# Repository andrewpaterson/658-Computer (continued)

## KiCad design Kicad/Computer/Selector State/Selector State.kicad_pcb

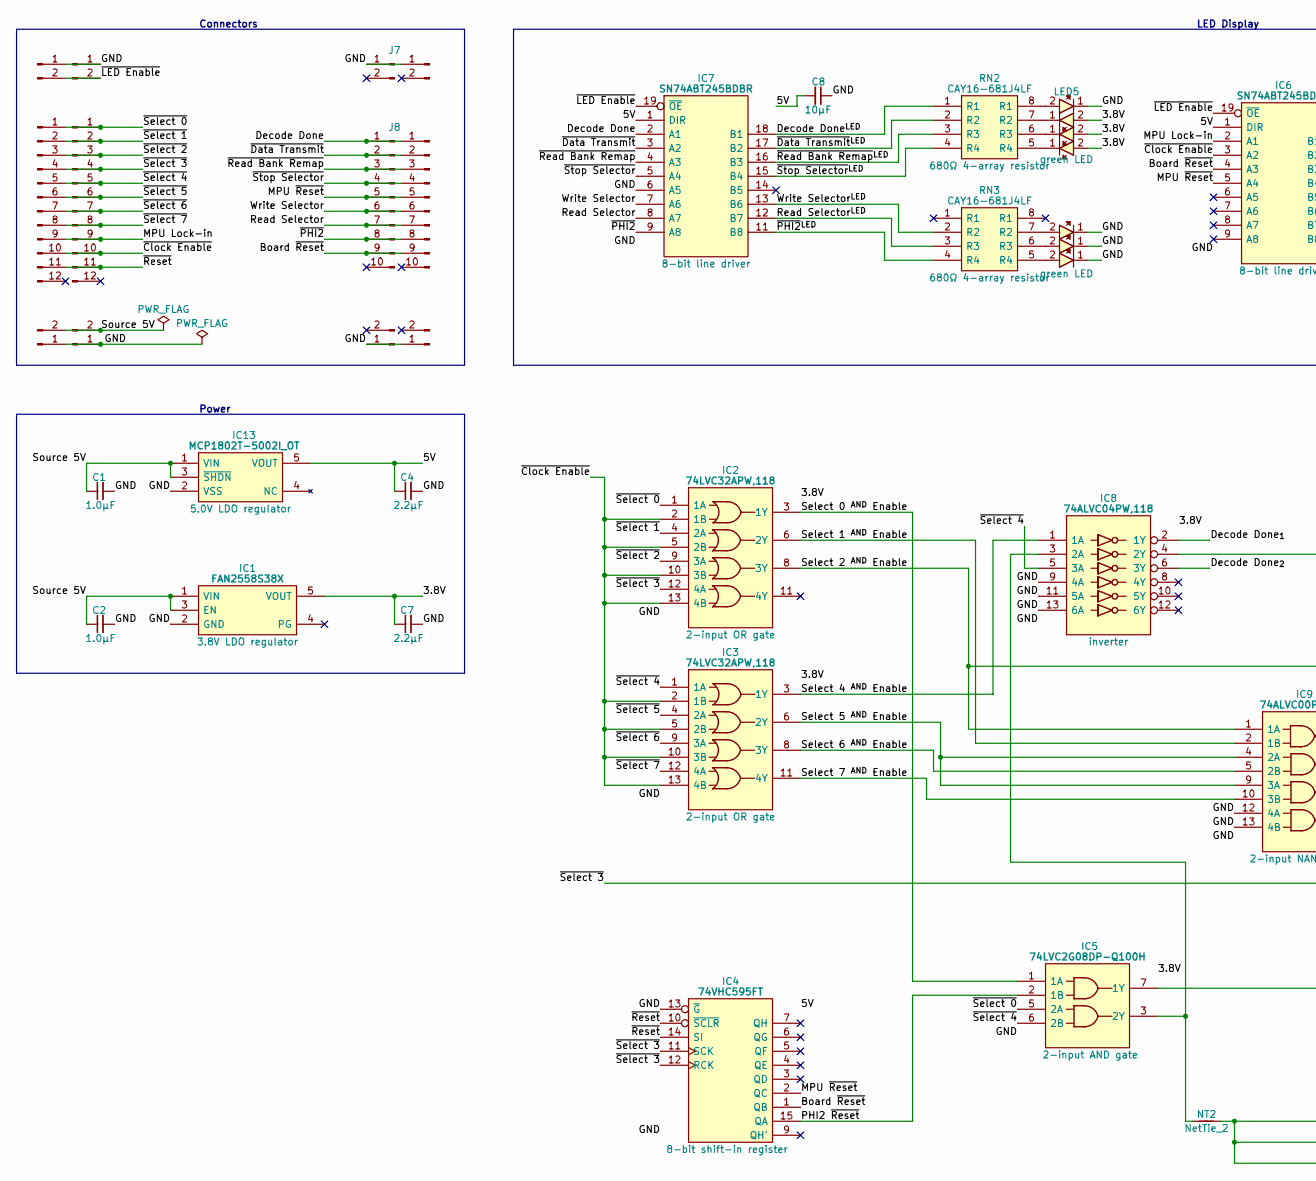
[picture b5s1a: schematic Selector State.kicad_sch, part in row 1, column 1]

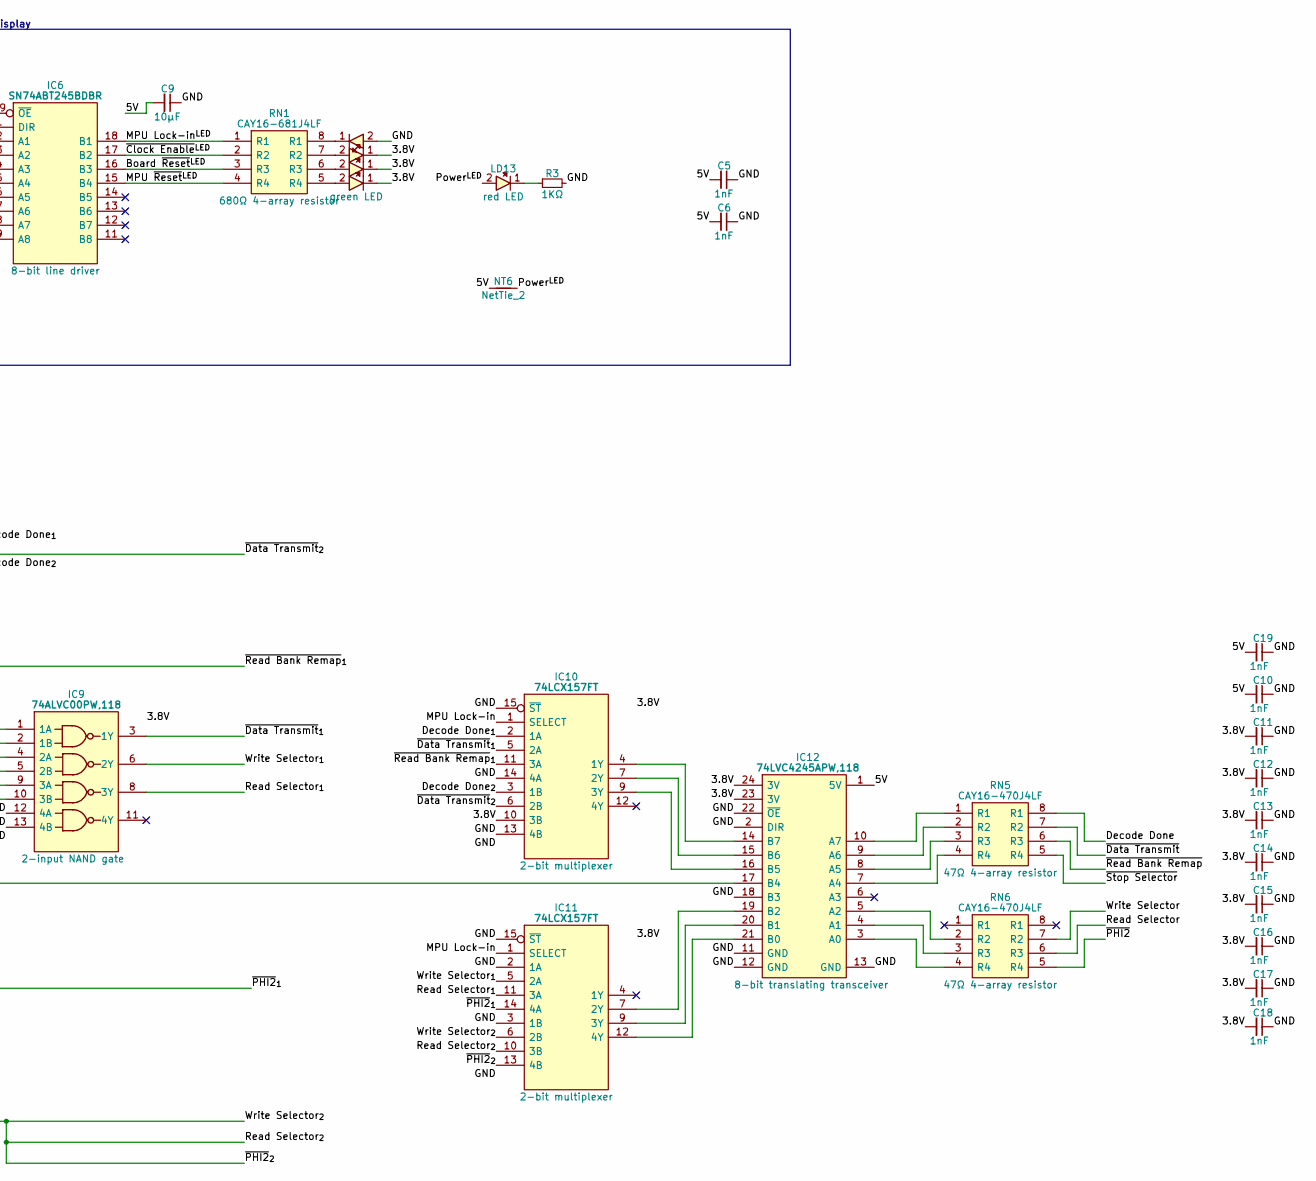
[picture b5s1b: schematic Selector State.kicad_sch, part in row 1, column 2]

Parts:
C1, C2, C4, C7: C_0805
C5, C6, C8, C9, C10, C11, C12, C13, C14, C15, C16, C17, C18, C19: C_Small; C_0805_2012Metric
IC1: FAN2558S38X; SOT95P270X145-5N; Manufacturer_Part_Number FAN2558S38X; Mouser Part Number 512-FAN2558S38X
IC2, IC3: 74LVC32APW,118; SOP65P640X110-14N; Manufacturer_Part_Number 74LVC32APW,118; Mouser Part Number 771-74LVC32APW-T
IC4: 74VHC595FT; SOP65P640X120-16N; Manufacturer_Part_Number 74VHC595FT; Mouser Part Number 757-74VHC595FT
IC5: 74LVC2G08DP-Q100H; SOP65P400X110-8N; Manufacturer_Part_Number 74LVC2G08DP-Q100H; Mouser Part Number 771-74LVC2G08DPQ100H
IC6, IC7: SN74ABT245BDBR; SOP65P780X200-20N; Manufacturer_Part_Number SN74ABT245BDBR; Mouser Part Number 595-SN74ABT245BDBR
IC8: 74ALVC04PW,118; SOP65P640X110-14N; Manufacturer_Part_Number 74ALVC04PW,118; Mouser Part Number 771-ALVC04PW118
IC9: 74ALVC00PW,118; SOP65P640X110-14N; Mouser Part Number 771-ALVC00PW118
IC10, IC11: 74LCX157FT; SOP65P640X120-16N; Manufacturer_Part_Number 74LCX157FT; Mouser Part Number 757-74LCX157FT
IC12: 74LVC4245APW,118; SOP65P640X110-24N; Mouser Part Number 771-74LVC4245APW-T
IC13: MCP1802T-5002I_OT; SOT95P270X145-5N; Manufacturer_Part_Number MCP1802T-5002I/OT; Mouser Part Number 579-MCP1802T-5002IOT
J1, J3, J4, J6, J7, J9, J10, J12: Conn_01x02_Male; PinHeader_1x02_P2.54mm_Vertical
J2, J5: Conn_01x12_Male; PinHeader_1x12_P2.54mm_Vertical
J8, J11: Conn_01x10_Male; PinHeader_1x10_P2.54mm_Vertical
LD10, LD11, LD12: 150224VS73100A; Manufacturer_Part_Number 150224VS73100A; Mouser Part Number 710-150224VS73100A
LD13: 150224SS73100; 150224SS73100A; Manufacturer_Part_Number 150224SS73100; Mouser Part Number 710-150224SS73100
LED1, LED2, LED3, LED4, LED5, LED6, LED7, LED8: 150224VS73100A; Manufacturer_Part_Number 150224VS73100A; Mouser Part Number 710-150224VS73100A
NT2, NT6: NetTie_2; NetTie-2_SMD_Pad0.5mm
R3: R_0805
RN1, RN2, RN3: CAY16-681J4LF; CAY16-J4; Manufacturer_Part_Number CAY16-681J4LF; Mouser Part Number 652-CAY16-681J4LF
RN5, RN6: CAY16-470J4LF; CAY16470J4LF; Manufacturer_Part_Number CAY16-470J4LF; Mouser Part Number 652-CAY16-470J4LF

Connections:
/3.8V: C7.1, C11.2, C12.2, C13.2, C14.2, C15.2, C16.2, C17.2, C18.2, IC1.5 (VOUT), IC2.14 (3V), IC3.14 (3V), IC5.8 (3V), IC8.14 (3V), IC9.14 (3V), IC10.10 (3B), IC10.16 (3V), IC11.16 (3V), IC12.23 (3V), IC12.24 (3V), LED2.1, LED3.1, LED4.1, LED6.2, LED7.2, LED8.2
/5V: C4.1, C5.2, C6.2, C8.2, C9.2, C10.2, C19.2, IC4.16 (5V), IC6.1 (DIR), IC6.20 (5V), IC7.1 (DIR), IC7.20 (5V), IC12.1 (5V), IC13.5 (VOUT), NT6.1
/Board ~Reset: IC4.1 (QB), IC6.4 (A3), J8.9, J11.9
/Board ~Reset^{LED}: IC6.16 (B3), RN1.3 (R3)
/Decode Done: IC7.2 (A1), J8.1, J11.1, RN5.8 (R1)
/Decode Done^{LED}: IC7.18 (B1), RN2.1 (R1)
/Decode Done_{1}: IC8.2 (1Y), IC10.2 (1A)
/Decode Done_{2}: IC8.6 (3Y), IC10.3 (1B)
/GND: C1.2, C2.2, C4.2, C5.1, C6.1, C7.2, C8.1, C9.1, C10.1, C11.1, C12.1, C13.1, C14.1, C15.1, C16.1, C17.1, C18.1, C19.1, IC1.2 (GND), IC2.7 (GND), IC3.7 (GND), IC4.8 (GND), IC4.13 (~G), IC5.4 (GND), IC6.10 (GND), IC7.6 (A5), IC7.10 (GND), IC8.7 (GND), IC8.9 (4A), IC8.11 (5A), IC8.13 (6A), IC9.7 (GND), IC9.12 (4A), IC9.13 (4B), IC10.8 (GND), IC10.13 (4B), IC10.14 (4A), IC10.15 (~ST), IC11.2 (1A), IC11.3 (1B), IC11.8 (GND), IC11.15 (~ST), IC12.2 (DIR), IC12.11 (GND), IC12.12 (GND), IC12.13 (GND), IC12.18 (B3), IC12.22 (~OE), IC13.2 (VSS), J1.1, J3.1, J4.1, J6.1, J7.1, J9.1, J10.1, J12.1, LD10.1, LD11.1, LD12.1, LED1.2, LED5.1, R3.2
/MPU Lock-in: IC6.2 (A1), IC10.1 (SELECT), IC11.1 (SELECT), J2.9, J5.9
/MPU Lock-in^{LED}: IC6.18 (B1), RN1.1 (R1)
/MPU ~Reset: IC4.2 (QC), IC6.5 (A4), J8.5, J11.5
/MPU ~Reset^{LED}: IC6.15 (B4), RN1.4 (R4)
/PHI2 ~Reset: IC4.15 (QA), IC5.2 (1B)
/Power^{LED}: LD13.2, NT6.2
/Read Selector: IC7.8 (A7), J8.7, J11.7, RN6.6 (R3)
/Read Selector^{LED}: IC7.12 (B7), RN3.3 (R3)
/Read Selector_{1}: IC9.8 (3Y), IC11.11 (3A)
/Select 0 ^{AND} Enable: IC2.3 (1Y), IC5.1 (1A)
/Select 1 ^{AND} Enable: IC2.6 (2Y), IC9.2 (1B)
/Select 2 ^{AND} Enable: IC2.8 (3Y), IC9.1 (1A), IC10.11 (3A)
/Select 4 ^{AND} Enable: IC3.3 (1Y), IC8.1 (1A)
/Select 5 ^{AND} Enable: IC3.6 (2Y), IC9.4 (2A), IC9.9 (3A)
/Select 6 ^{AND} Enable: IC3.8 (3Y), IC9.5 (2B)
/Select 7 ^{AND} Enable: IC3.11 (4Y), IC9.10 (3B)
/Source 5V: C1.1, C2.1, IC1.1 (VIN), IC1.3 (EN), IC13.1 (VIN), IC13.3 (~SHDN), J3.2, J6.2
/Write Selector: IC7.7 (A6), J8.6, J11.6, RN6.7 (R2)
/Write Selector^{LED}: IC7.13 (B6), RN3.2 (R2)
/Write Selector_{1}: IC9.6 (2Y), IC11.5 (2A)
/Write Selector_{2}: IC11.6 (2B), IC11.10 (3B), IC11.13 (4B), NT2.2
/~Clock Enable: IC2.2 (1B), IC2.5 (2B), IC2.10 (3B), IC2.13 (4B), IC3.2 (1B), IC3.5 (2B), IC3.10 (3B), IC3.13 (4B), IC6.3 (A2), J2.10, J5.10
/~Clock Enable^{LED}: IC6.17 (B2), RN1.2 (R2)
/~Data Transmit: IC7.3 (A2), J8.2, J11.2, RN5.7 (R2)
/~Data Transmit^{LED}: IC7.17 (B2), RN2.2 (R2)
/~Data Transmit_{1}: IC9.3 (1Y), IC10.5 (2A)
/~Data Transmit_{2}: IC8.4 (2Y), IC10.6 (2B)
/~LED Enable: IC6.19 (~OE), IC7.19 (~OE), J1.2, J4.2
/~PHI2: IC7.9 (A8), J8.8, J11.8, RN6.5 (R4)
/~PHI2^{LED}: IC7.11 (B8), RN3.4 (R4)
/~PHI2_{1}: IC5.7 (1Y), IC11.14 (4A)
/~Read Bank Remap: IC7.4 (A3), J8.3, J11.3, RN5.6 (R3)
/~Read Bank Remap^{LED}: IC7.16 (B3), RN2.3 (R3)
/~Reset: IC4.10 (~SCLR), IC4.14 (SI), J2.11, J5.11
/~Select 0: IC2.1 (1A), IC5.5 (2A), J2.1, J5.1
/~Select 1: IC2.4 (2A), J2.2, J5.2
/~Select 2: IC2.9 (3A), J2.3, J5.3
/~Select 3: IC2.12 (4A), IC4.11 (SCK), IC4.12 (RCK), IC12.17 (B4), J2.4, J5.4
/~Select 4: IC3.1 (1A), IC5.6 (2B), IC8.5 (3A), J2.5, J5.5
/~Select 5: IC3.4 (2A), J2.6, J5.6
/~Select 6: IC3.9 (3A), J2.7, J5.7
/~Select 7: IC3.12 (4A), J2.8, J5.8
/~Stop Selector: IC7.5 (A4), J8.4, J11.4, RN5.5 (R4)
/~Stop Selector^{LED}: IC7.15 (B4), RN2.4 (R4)
unnamed: IC5.3 (2Y), IC8.3 (2A), NT2.1
unnamed: IC10.4 (1Y), IC12.14 (B7)
unnamed: IC10.7 (2Y), IC12.15 (B6)
unnamed: IC10.9 (3Y), IC12.16 (B5)
unnamed: IC11.7 (2Y), IC12.19 (B2)
unnamed: IC11.9 (3Y), IC12.20 (B1)
unnamed: IC11.12 (4Y), IC12.21 (B0)
unnamed: IC12.3 (A0), RN6.4 (R4)
unnamed: IC12.4 (A1), RN6.3 (R3)
unnamed: IC12.5 (A2), RN6.2 (R2)
unnamed: IC12.7 (A4), RN5.4 (R4)
unnamed: IC12.8 (A5), RN5.3 (R3)
unnamed: IC12.9 (A6), RN5.2 (R2)
unnamed: IC12.10 (A7), RN5.1 (R1)
unnamed: LD10.2, RN3.7 (R2)
unnamed: LD13.1, R3.1
unnamed: LED1.1, RN1.8 (R1)
unnamed: LED2.2, RN1.7 (R2)
unnamed: LED3.2, RN1.6 (R3)
unnamed: LED4.2, RN1.5 (R4)
unnamed: LED5.2, RN2.8 (R1)
unnamed: LED8.1, RN2.5 (R4)
unnamed: LED7.1, RN2.6 (R3)
unnamed: LED6.1, RN2.7 (R2)
unnamed: LD12.2, RN3.5 (R4)
unnamed: LD11.2, RN3.6 (R3)

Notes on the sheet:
LED Display
Power
Connectors

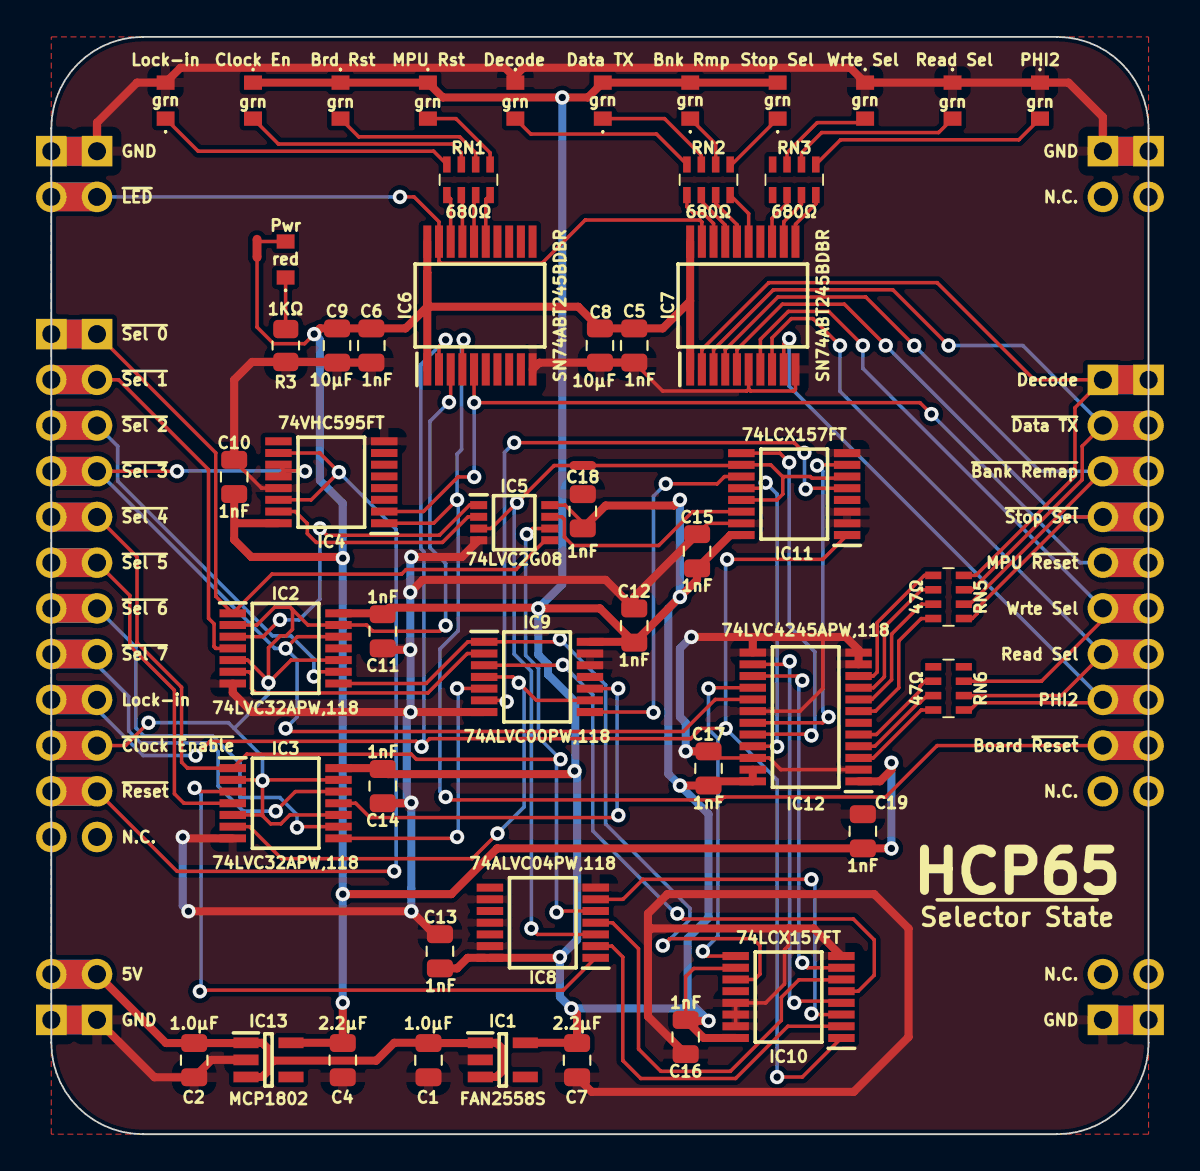
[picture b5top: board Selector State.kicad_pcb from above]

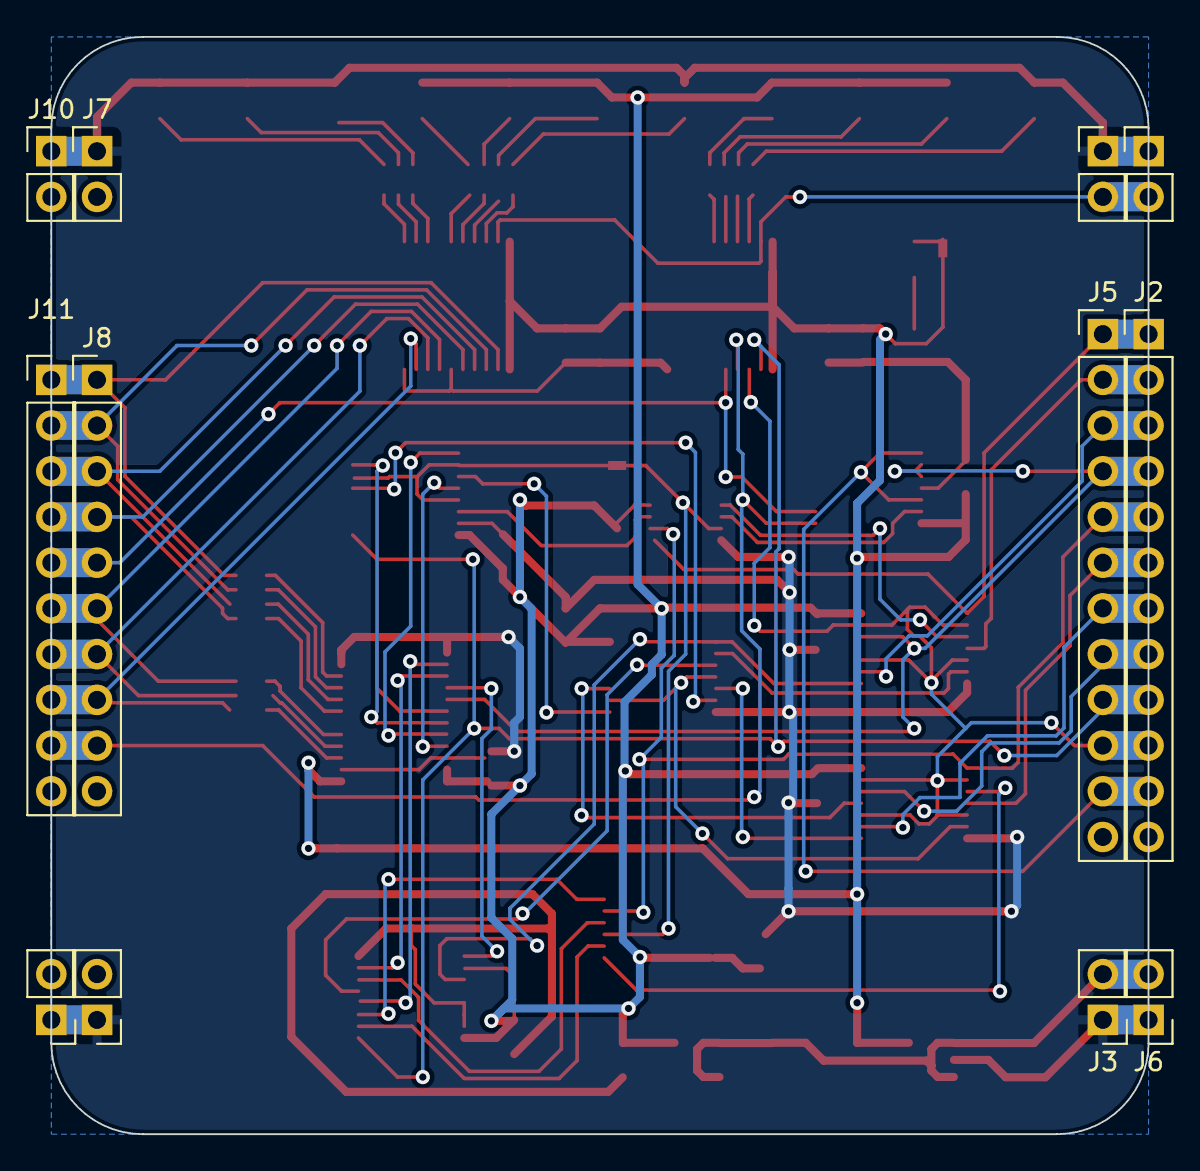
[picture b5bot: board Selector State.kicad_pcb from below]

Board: 2 copper layers, 61.0 x 61.0 mm, 63 parts (12 on the bottom side), 79 nets.
